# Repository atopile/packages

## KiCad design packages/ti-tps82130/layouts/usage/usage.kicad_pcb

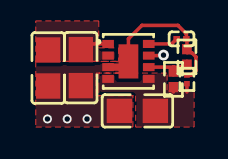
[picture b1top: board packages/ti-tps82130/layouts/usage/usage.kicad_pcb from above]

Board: 2 copper layers, 8 parts (0 on the bottom side), 6 nets.

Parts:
C1, C4: 4.7µF ±10%; C0805
C2: 47µF ±20%; C0805
C3: 1nF ±10%; C0201
R1: 100kΩ ±1%; R0201
R2: 3.57kΩ ±1%; R0402
R3: 1.15kΩ ±1%; R0402
U1: USIP-8_L3.0-W2.8-P0.65-TL-EP

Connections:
hv: C1.1, C4.1, U1.1, U1.2
lv: C1.2, C3.2, C4.2, U1.3, U1.9
power-hv: C3.1, U1.8
power_out-hv: C2.1, R1.1, R2.1, U1.4, U1.5
power_out-lv: C2.2, R1.2, R3.2
ref_out-hv: R2.2, R3.1, U1.6

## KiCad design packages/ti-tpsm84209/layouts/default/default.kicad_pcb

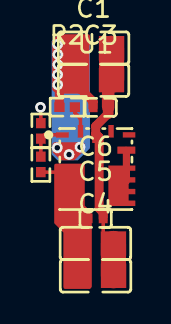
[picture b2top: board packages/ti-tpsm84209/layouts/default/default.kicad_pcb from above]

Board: 2 copper layers, 10 parts (0 on the bottom side), 7 nets.

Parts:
C1, C2: 0.00001F; C0805
C3, C6: 0.0000001F; C0402
C4, C5: 0.000022F; C0805
R1: 10000Ω; R0402
R2: 100000Ω; R0402
R3: 52300Ω; R0402
U1: QFN-9_L4.5-W4.0_TPSM84209RKHR

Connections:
DNC: U1.6, U1.7
EN: R2.2, U1.9
FB: R1.1, R3.2, U1.1
SW: U1.4, U1.5
cout_hf-power-hv: C4.1, C5.1, C6.1, R3.1, U1.3
hv: C1.1, C2.1, C3.1, R2.1, U1.2
lv: C1.2, C2.2, C3.2, C4.2, C5.2, C6.2, R1.2, U1.8

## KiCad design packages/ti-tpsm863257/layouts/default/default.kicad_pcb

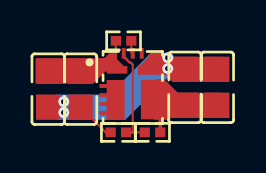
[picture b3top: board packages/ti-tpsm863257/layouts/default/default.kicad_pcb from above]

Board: 2 copper layers, 8 parts (0 on the bottom side), 5 nets.

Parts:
C1, C2: 10µF ±10%; C0805
C3, C4: 22µF ±20%; C0805
R1: 22.1kΩ ±1%; R0402
R2: 28kΩ ±1%; R0402
R3: 10kΩ ±1%; R0402
U1: QFN-7_L4.0-W3.3_TPSM863257RDXR

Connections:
EN: R3.2, U1.6
hv: C1.1, C2.1, R3.1, U1.1
lv: C1.2, C2.2, C3.2, C4.2, R2.2, U1.4
output_caps[1]-power-hv: C3.1, C4.1, R1.1, U1.3
ref_out-hv: R1.2, R2.1, U1.7

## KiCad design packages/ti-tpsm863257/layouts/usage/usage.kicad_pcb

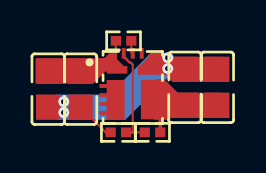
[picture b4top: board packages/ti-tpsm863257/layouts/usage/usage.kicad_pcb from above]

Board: 2 copper layers, 8 parts (0 on the bottom side), 5 nets.

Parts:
C1, C2: 10µF ±10%; C0805
C3, C4: 22µF ±20%; C0805
R1: 10kΩ ±1%; R0402
R2: 11.5kΩ ±1%; R0402
R3: 2.55kΩ ±1%; R0402
U1: QFN-7_L4.0-W3.3_TPSM863257RDXR

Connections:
EN: R1.2, U1.6
hv: C1.1, C2.1, R1.1, U1.1
lv: C1.2, C2.2, C3.2, C4.2, R3.2, U1.4
output_caps[1]-power-hv: C3.1, C4.1, R2.1, U1.3
ref_out-hv: R2.2, R3.1, U1.7

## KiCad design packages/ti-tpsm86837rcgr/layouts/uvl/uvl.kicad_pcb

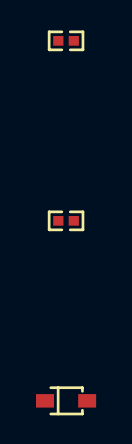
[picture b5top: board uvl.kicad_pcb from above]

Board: 2 copper layers, 3 parts (0 on the bottom side), 2 nets, no tracks yet.

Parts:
D1: Vf ℝ+V; SOD-323_L1.8-W1.3-LS2.5-RD
R1, R2: 10000Ω; R0402

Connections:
anode: D1.2, R2.2
cathode: D1.1, R1.2, R2.1
